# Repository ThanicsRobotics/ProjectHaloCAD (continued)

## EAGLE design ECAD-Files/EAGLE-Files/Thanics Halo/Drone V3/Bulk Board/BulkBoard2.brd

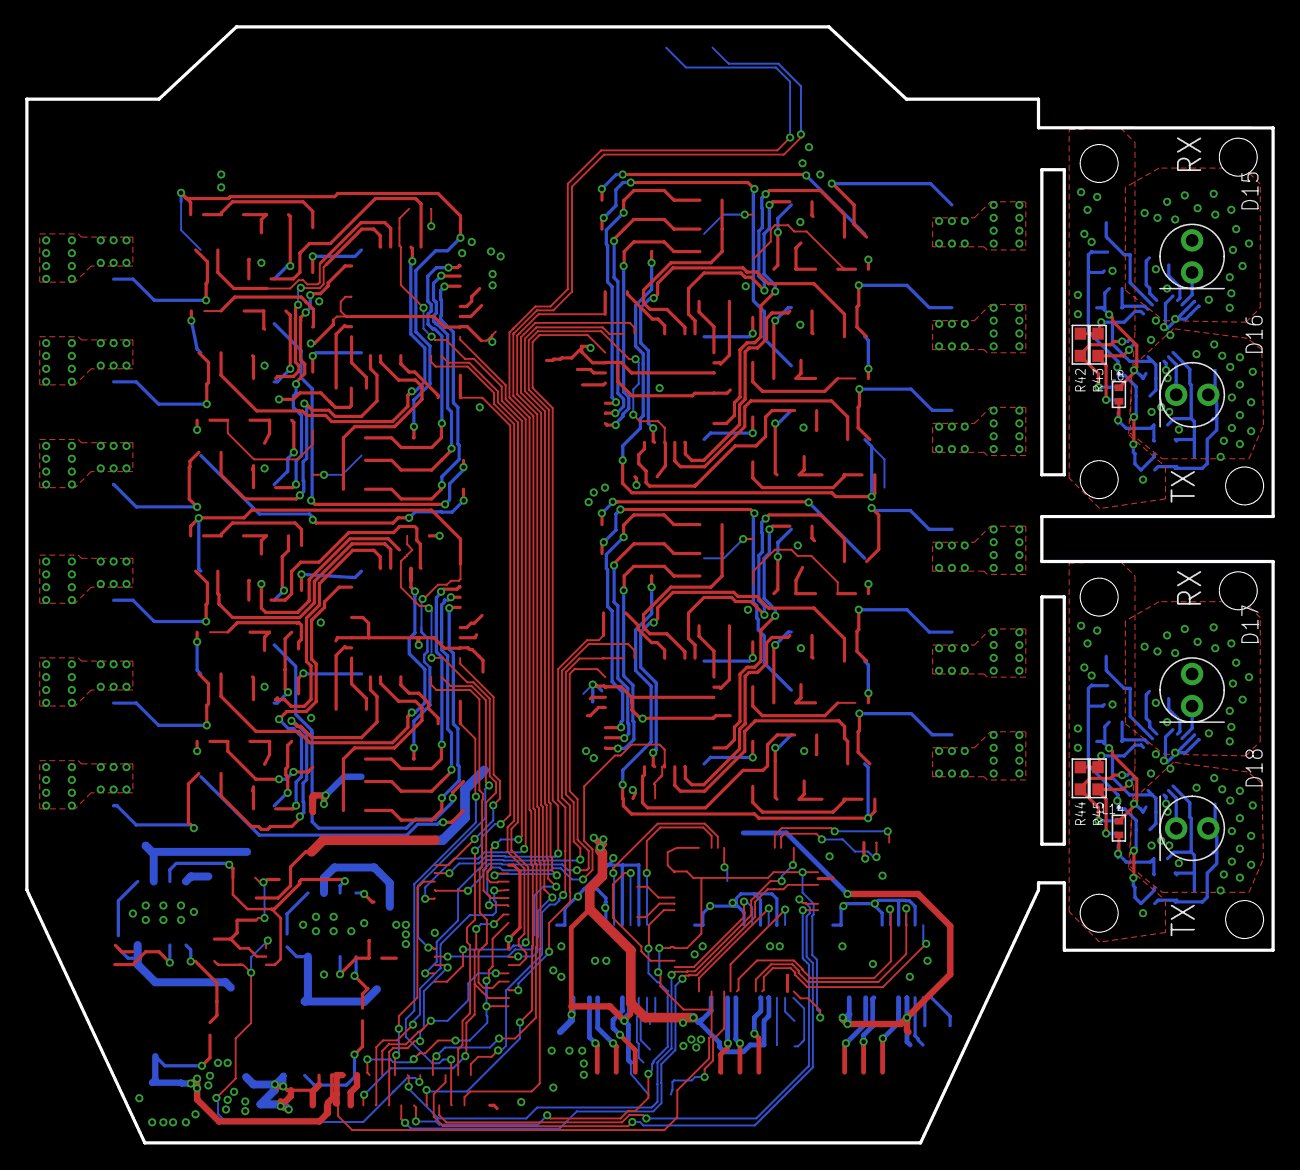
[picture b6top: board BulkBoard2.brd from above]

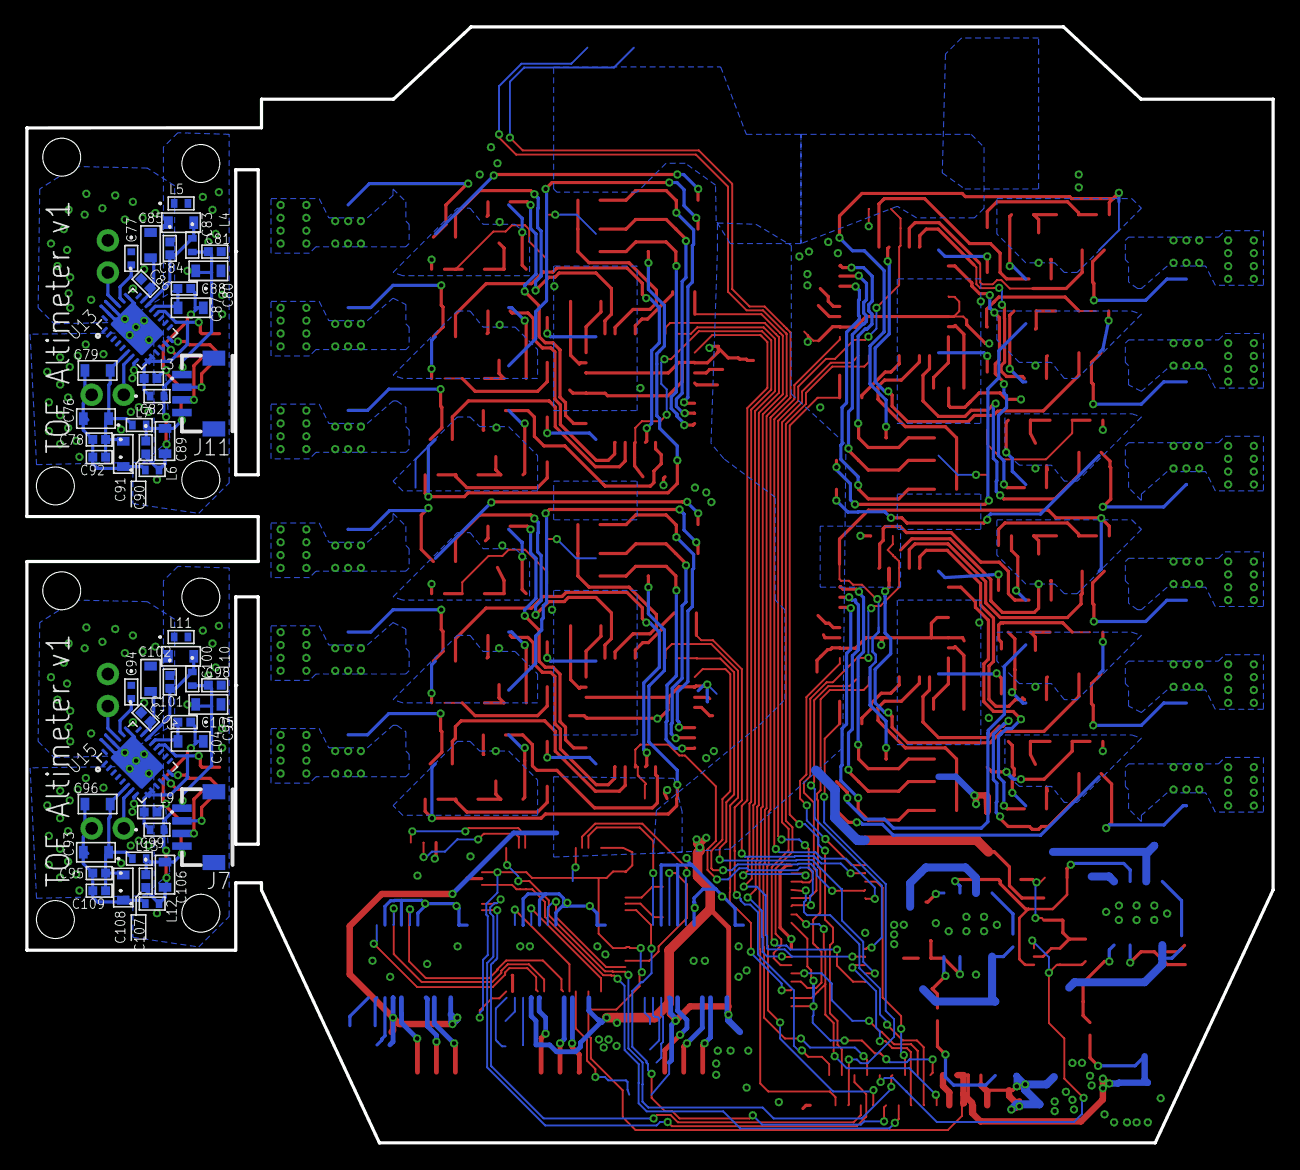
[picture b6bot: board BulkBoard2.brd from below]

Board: 4 copper layers, 98.6 x 88.3 mm, 58 parts (48 on the bottom side), 30 nets.

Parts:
C76, C79, C80, C83, C85, C87, C89, C91, C93, C96, C97, C100, C102, C104, C106, C108: 1uF; 0603_CAPACITOR
C77, C94: 6pF; 0402_CAPACITOR
C78, C81, C82, C84, C86, C88, C90, C92, C95, C98, C99, C101, C103, C105, C107, C109: 0.1uF; 0402-M
D15, D17: SFH203FA; 5MM_LED
D16, D18: SFH4550; 5MM_LED
J7, J11: JST_SH_4POS
L3, L4, L5, L6, L7, L8, L9, L10, L11, L12, L13, L14: MMZ1005S182ET000IND_1005-M; IND_1005-M
R42, R43, R44, R45: 1k; RC0603N-M
U13, U15: OPT3101; 28-VQFN

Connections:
+3V1: C80.1, C81.2, C89.1, C90.2, J11.1, L3.2, L4.2, L6.2
+3V2: C87.1, C88.2, U13.19
+3V4: C97.1, C98.2, C106.1, C107.2, J7.1, L9.2, L10.2, L12.2
+3V5: C104.1, C105.2, U15.19
AGND: C77.1, C83.2, C84.1, C85.2, C86.1, D15.A, L5.1, U13.23, U13.26, U13.27, U13.29
AGND1: C94.1, C100.2, C101.1, C102.2, C103.1, D17.A, L11.1, U15.23, U15.26, U15.27, U15.29
AVCC: C83.1, C84.2, L4.1, U13.20
AVCC1: C100.1, C101.2, L10.1, U15.20
GND1: C80.2, C81.1, C89.2, C90.1, J11.4, J11.P$5, J11.P$6, L5.2, L7.2, L8.2
GND2: C97.2, C98.1, C106.2, C107.1, J7.4, J7.P$5, J7.P$6, L11.2, L13.2, L14.2
GNDIO: C82.1, C87.2, C88.1, L8.1, U13.3, U13.4, U13.5, U13.8
GNDIO1: C99.1, C104.2, C105.1, L14.1, U15.3, U15.4, U15.5, U15.8
I2C_SCL: J11.3, R43.2, U13.13
I2C_SCL1: J7.3, R45.2, U15.13
I2C_SDA: J11.2, R42.2, U13.14
I2C_SDA1: J7.2, R44.2, U15.14
unnamed: D16.C, U13.7
unnamed: C77.2, U13.24
unnamed: D15.C, U13.25
unnamed: C85.1, C86.2, U13.21
unnamed: D18.C, U15.7
unnamed: C94.2, U15.24
unnamed: D17.C, U15.25
unnamed: C102.1, C103.2, U15.21
VCCIO: C82.2, L3.1, R42.1, R43.1, U13.9, U13.10, U13.18
VCCIO1: C99.2, L9.1, R44.1, R45.1, U15.9, U15.10, U15.18
VDDLED: C76.2, C78.2, C79.2, C91.1, C92.2, D16.A, L6.1
VDDLED1: C93.2, C95.2, C96.2, C108.1, C109.2, D18.A, L12.1
VSS: C76.1, C78.1, C79.1, C91.2, C92.1, L7.1, U13.6
VSS1: C93.1, C95.1, C96.1, C108.2, C109.1, L13.1, U15.6

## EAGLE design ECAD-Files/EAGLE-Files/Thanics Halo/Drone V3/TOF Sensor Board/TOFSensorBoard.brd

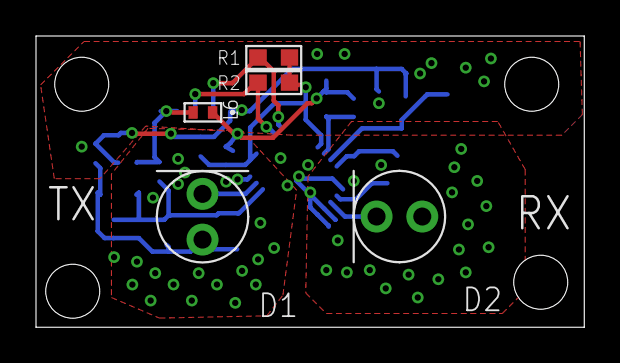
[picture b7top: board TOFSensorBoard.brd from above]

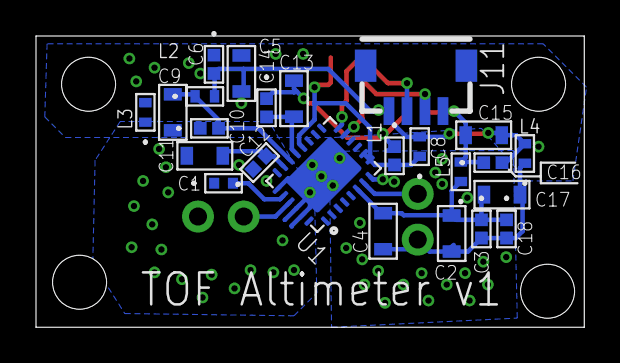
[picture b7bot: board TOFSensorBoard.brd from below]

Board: 4 copper layers, 30.5 x 16.2 mm, 29 parts (24 on the bottom side), 15 nets.

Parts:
C1: 6pF; 0402_CAPACITOR
C2, C4, C5, C9, C11, C13, C15, C17: 1uF; 0603_CAPACITOR
C3, C6, C8, C10, C12, C14, C16, C18: 0.1uF; 0402-M
D1: SFH4550; 5MM_LED
D2: SFH203FA; 5MM_LED
J11: JST_SH_4POS
L1, L2, L3, L4, L5, L6: MMZ1005S182ET000IND_1005-M; IND_1005-M
R1, R2: 1k; RC0603N-M
U1: OPT3101; 28-VQFN

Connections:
+3V1: C13.1, C14.2, U1.19
+3V3: C5.1, C6.2, C15.1, C16.2, J11.1, L1.2, L2.2, L4.2
AGND: C1.1, C9.2, C10.1, C11.2, C12.1, D2.A, L3.1, U1.23, U1.26, U1.27, U1.29
AVCC: C9.1, C10.2, L2.1, U1.20
GND: C5.2, C6.1, C15.2, C16.1, J11.4, J11.P$5, J11.P$6, L3.2, L5.2, L6.2
GNDIO: C8.1, C13.2, C14.1, L6.1, U1.3, U1.4, U1.5, U1.8
I2C_SCL: J11.3, R2.2, U1.13
I2C_SDA: J11.2, R1.2, U1.14
unnamed: C11.1, C12.2, U1.21
unnamed: D1.C, U1.7
unnamed: C1.2, U1.24
unnamed: D2.C, U1.25
VCCIO: C8.2, L1.1, R1.1, R2.1, U1.9, U1.10, U1.18
VDDLED: C2.2, C3.2, C4.2, C17.1, C18.2, D1.A, L4.1
VSS: C2.1, C3.1, C4.1, C17.2, C18.1, L5.1, U1.6
